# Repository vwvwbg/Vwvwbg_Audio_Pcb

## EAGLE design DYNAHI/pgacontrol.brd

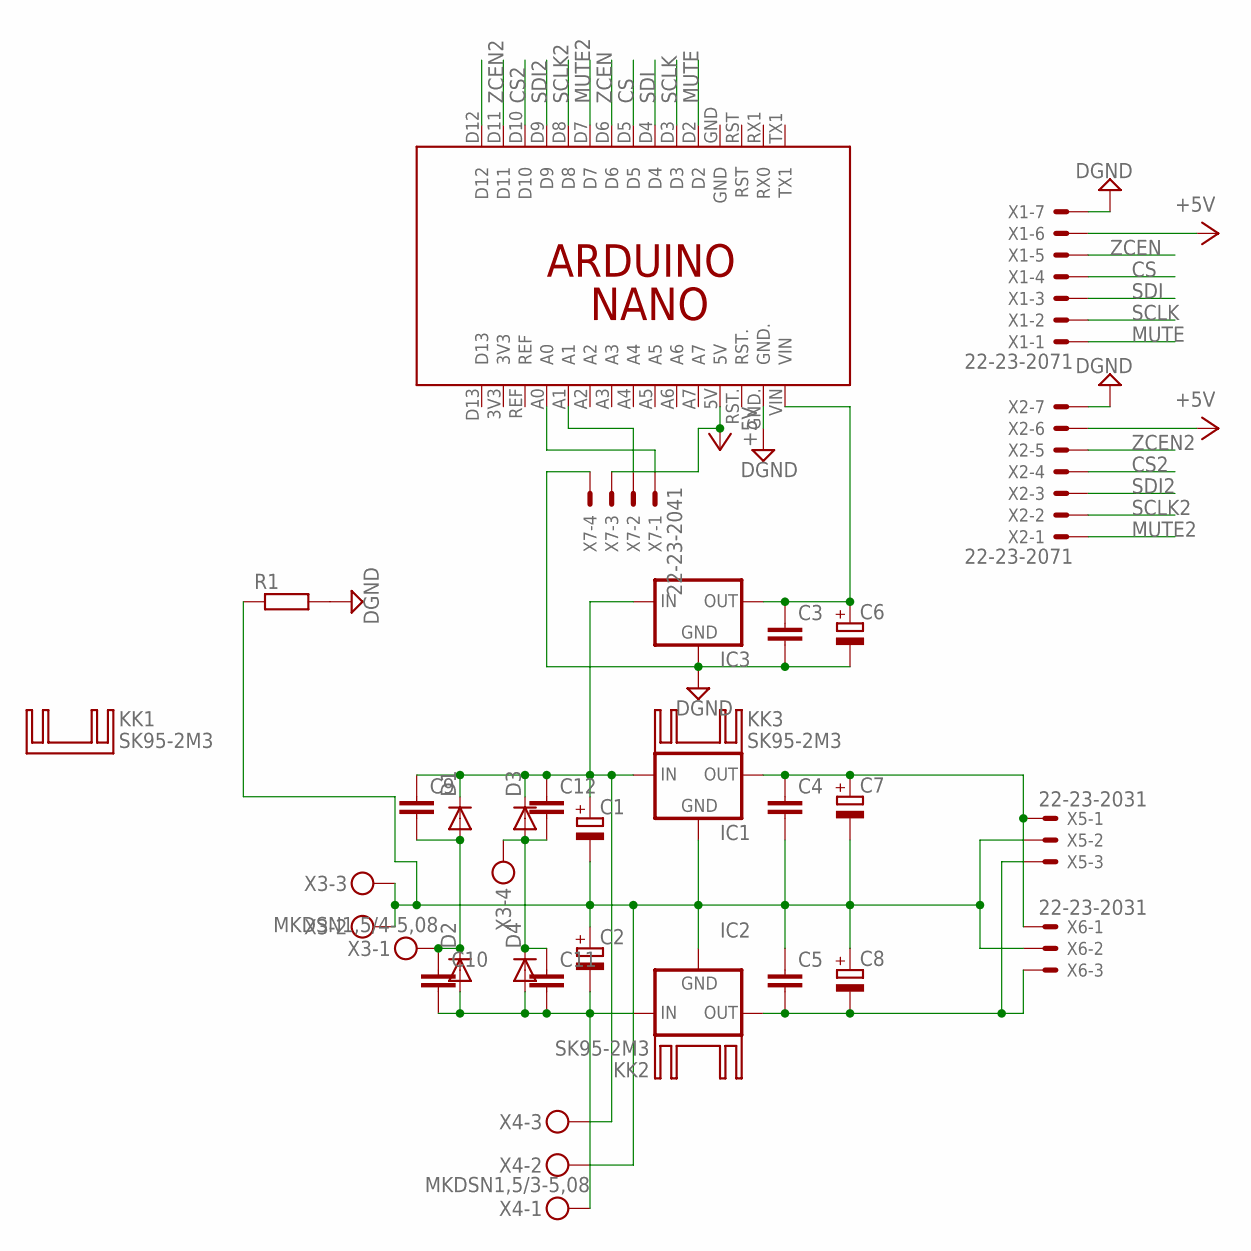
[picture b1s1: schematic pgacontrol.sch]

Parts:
C1, C2: CPOL-EUE7.5-18; E7,5-18
C3, C4, C5, C9, C10, C11, C12: C-EU050-030X075; C050-030X075
C6, C7, C8: CPOL-EUE3.5-8; E3,5-8
D1, D2, D3, D4: 1N4148DO35-10; DO35-10
IC1, IC3: 78XXS
IC2: 79XXS
KK1, KK2, KK3: SK95-2M3
PCB1: ARDUINO_NANO
R1: R-EU_0207/7; 0207/7
X1, X2: 22-23-2071
X3: MKDSN1,5/4-5,08
X4: MKDSN1,5/3-5,08
X5, X6: 22-23-2031
X7: 22-23-2041

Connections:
+5V: PCB1.5V, X1.6, X2.6, X7.3
+15: C4.1, C7.+, IC1.OUT, X5.1, X6.1
CS: PCB1.D5, X1.4
CS2: PCB1.D10, X2.4
DGND: C3.2, C6.-, IC3.GND, PCB1.GND., R1.2, X1.7, X2.7, X7.4
GND: C1.-, C2.+, C4.2, C5.1, C7.-, C8.+, IC1.GND, IC2.GND, R1.1, X3.2, X3.3, X4.2, X5.2, X6.2
MUTE: PCB1.D2, X1.1
MUTE2: PCB1.D7, X2.1
unnamed: C9.2, C10.1, D1.A, D2.C, X3.1
unnamed: PCB1.A0, X7.1
unnamed: C11.1, C12.2, D3.A, D4.C, X3.4
unnamed: PCB1.A1, X7.2
unnamed: C5.2, C8.-, IC2.OUT, X5.3, X6.3
unnamed: C3.1, C6.+, IC3.OUT, PCB1.VIN
SCLK: PCB1.D3, X1.2
SCLK2: PCB1.D8, X2.2
SDI: PCB1.D4, X1.3
SDI2: PCB1.D9, X2.3
V+: C1.+, C9.1, C12.1, D1.C, D3.C, IC1.IN, IC3.IN, X4.3
V-: C2.-, C10.2, C11.2, D2.A, D4.A, IC2.IN, X4.1
ZCEN: PCB1.D6, X1.5
ZCEN2: PCB1.D11, X2.5

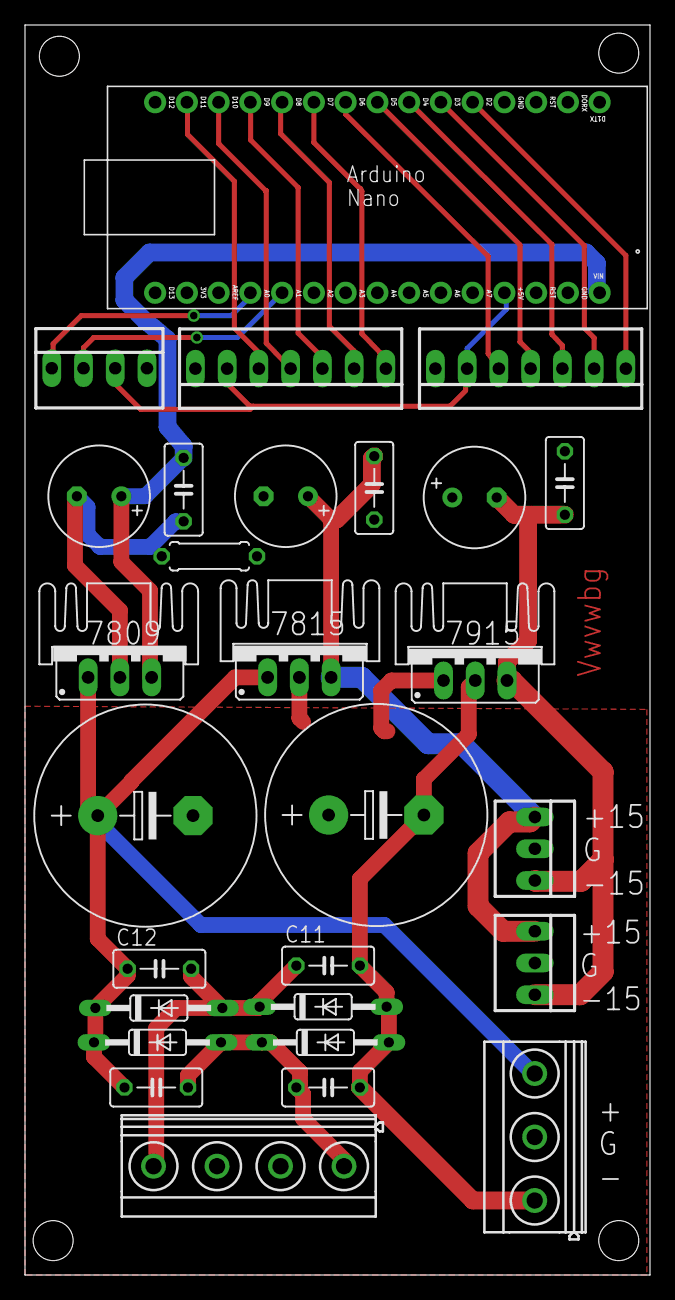
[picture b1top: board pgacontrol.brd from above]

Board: 2 copper layers, 50.0 x 100.0 mm, 31 parts (0 on the bottom side), 22 nets.

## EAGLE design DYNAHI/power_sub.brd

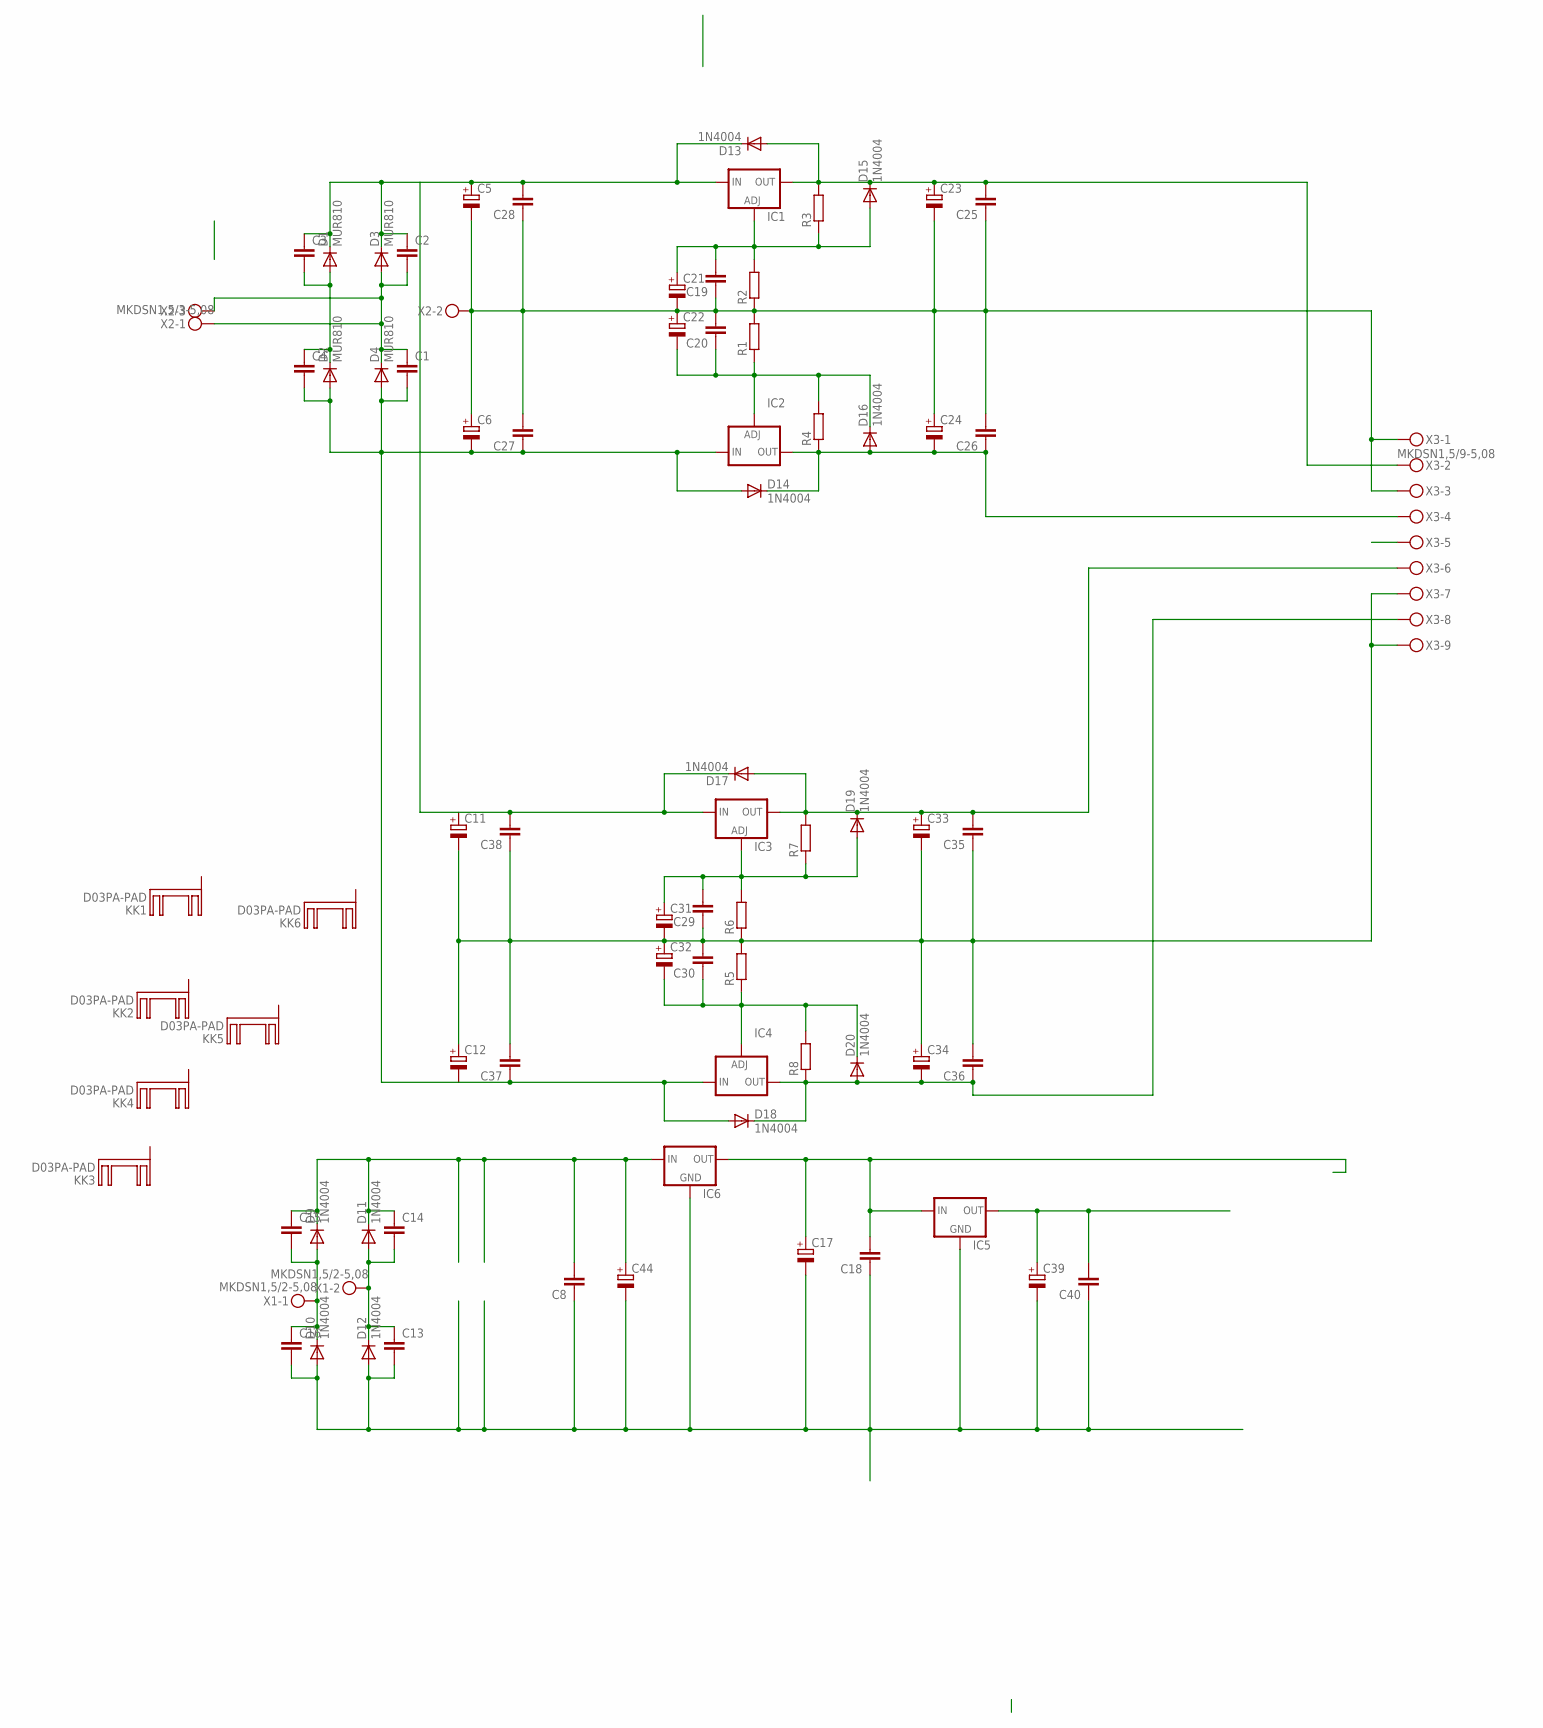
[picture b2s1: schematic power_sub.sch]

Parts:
C1, C2, C3, C4, C13, C14, C15, C16: C-EU025-025X050; C025-025X050
C5, C6, C11, C12, C44: CPOL-EUE7.5-18; E7,5-18
C8, C18, C19, C20, C25, C26, C27, C28, C29, C30, C35, C36, C37, C38, C40: C-EU050-045X075; C050-045X075
C17, C23, C24, C33, C34, C39: CPOL-EUE5-10.5; E5-10,5
C21, C22, C31, C32: CPOL-EUE5-8.5; E5-8,5
D1, D2, D3, D4: MUR810; TO220ACS
D9, D10, D11, D12, D13, D14, D15, D16, D17, D18, D19, D20: 1N4004; DO41-10
IC1, IC3: LM317TS; 317TS
IC2, IC4: LM337TS; 337TS
IC5, IC6: 78XXS
KK1, KK2, KK3, KK4, KK5, KK6: D03PA-PAD
R1, R2, R3, R4, R5, R6, R7, R8: R-EU_0207/12; 0207/12
X1: MKDSN1,5/2-5,08
X2: MKDSN1,5/3-5,08
X3: MKDSN1,5/9-5,08

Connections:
unnamed: C2.1, C3.1, C5.+, C28.2, C38.2, D1.C, D3.C, D13.C, D17.C, IC1.3 (IN), IC3.3 (IN)
unnamed: C3.2, C4.1, D1.A, D2.C
unnamed: C39.+, C40.2, IC5.OUT
unnamed: C1.1, C2.2, D3.A, D4.C, X2.1, X2.3
unnamed: C11.-, C12.+, C29.1, C30.2, C31.-, C32.+, C33.-, C34.+, C35.1, C36.2, C37.2, C38.1, R5.2, R6.1, X3.7, X3.9
unnamed: C8.2, C14.1, C15.1, C44.+, D9.C, D11.C, IC6.IN
unnamed: C15.2, C16.1, D9.A, D10.C, X1.1
unnamed: C8.1, C13.2, C16.2, C17.-, C18.1, C39.-, C40.1, C44.-, D10.A, D12.A, IC5.GND, IC6.GND
unnamed: C13.1, C14.2, D11.A, D12.C, X1.2
unnamed: C1.2, C4.2, C6.-, C27.1, C37.1, D2.A, D4.A, D14.A, D18.A, IC2.2 (IN), IC4.2 (IN)
unnamed: C23.+, C25.2, D13.A, D15.C, IC1.2 (OUT), R3.2, X3.2
unnamed: C33.+, C35.2, D17.A, D19.C, IC3.2 (OUT), R7.2, X3.6
unnamed: C20.1, C22.-, D16.C, IC2.1 (ADJ), R1.1, R4.2
unnamed: C19.2, C21.+, D15.A, IC1.1 (ADJ), R2.2, R3.1
unnamed: C5.-, C6.+, C19.1, C20.2, C21.-, C22.+, C23.-, C24.+, C25.1, C26.2, C27.2, C28.1, R1.2, R2.1, X2.2, X3.1, X3.3
unnamed: C30.1, C32.-, D20.C, IC4.1 (ADJ), R5.1, R8.2
unnamed: C29.2, C31.+, D19.A, IC3.1 (ADJ), R6.2, R7.1
unnamed: C17.+, C18.2, IC5.IN, IC6.OUT
unnamed: C24.-, C26.1, D14.C, D16.A, IC2.3 (OUT), R4.1, X3.4
unnamed: C34.-, C36.1, D18.C, D20.A, IC4.3 (OUT), R8.1, X3.8

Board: 2 copper layers, 77 parts (0 on the bottom side), 20 nets, no tracks yet.

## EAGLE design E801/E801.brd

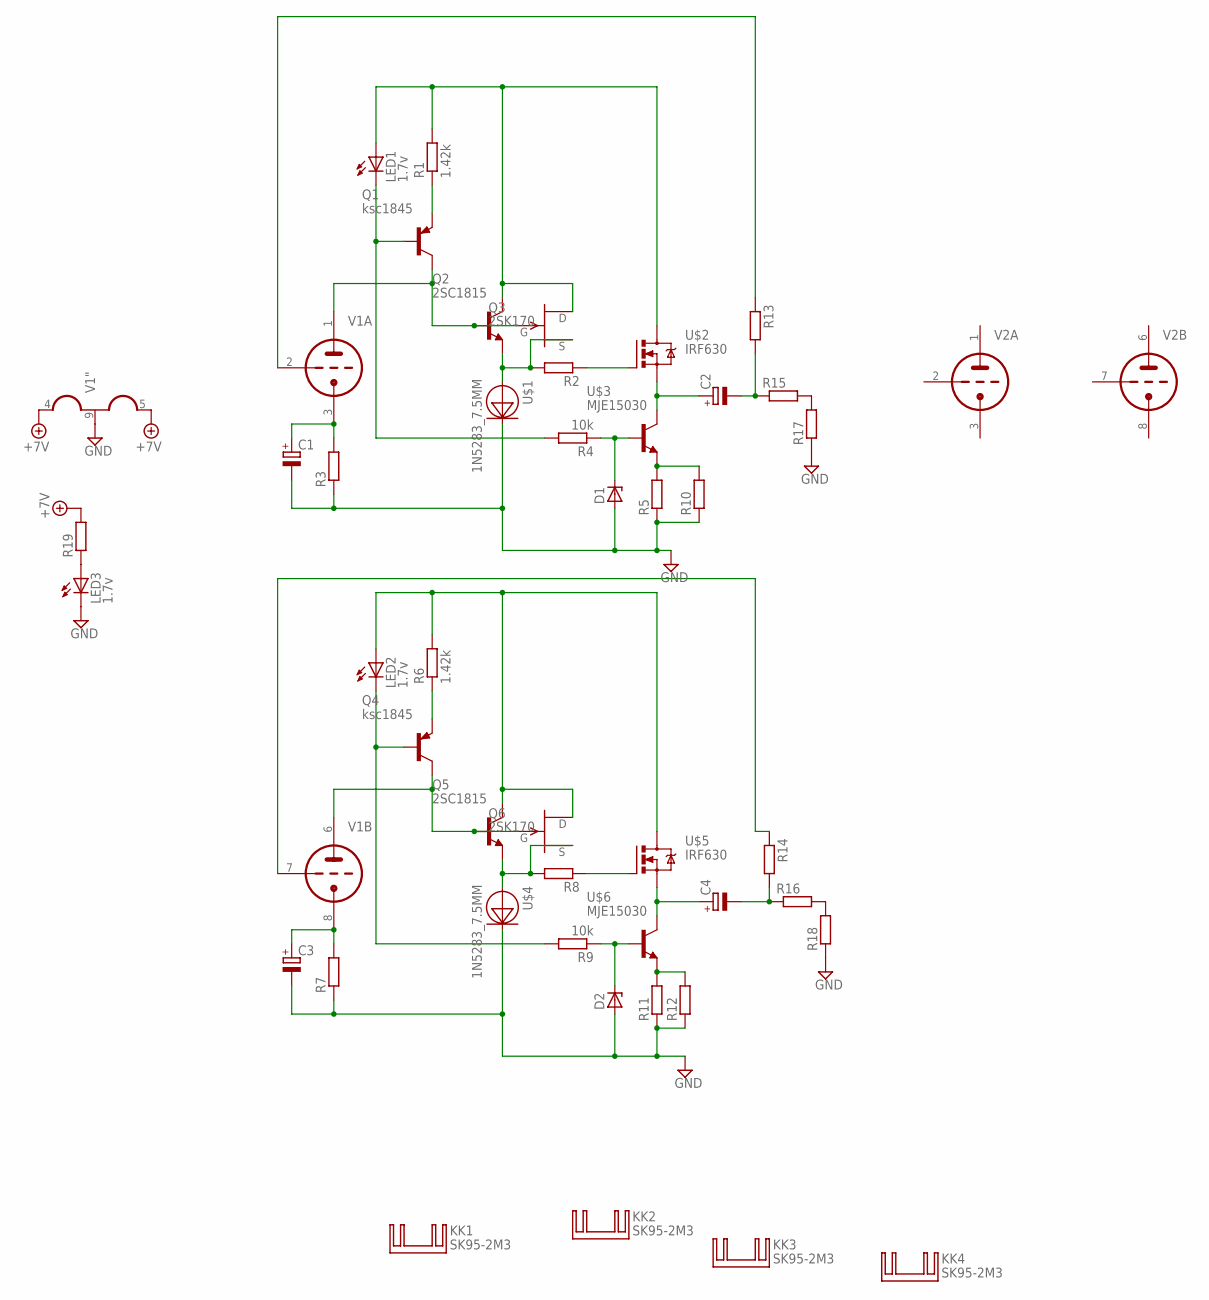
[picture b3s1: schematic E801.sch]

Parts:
C1, C3: CPOL-EUE5-10.5; E5-10,5
C2, C4: CPOL-EUE30-12AXIAL; E30-12
D1, D2: ZENER-DIODEDO34-7; DO34Z7
KK1, KK2, KK3, KK4: SK95-2M3
LED1, LED2, LED3: 1.7v; LED5MM
Q1, Q4: ksc1845; TO92-BCE
Q2, Q5: 2SC1815; TO92-ECB
Q3, Q6: 2SK170; TO92-
R1, R6: 1.42k; 0207/10
R2, R3, R5, R7, R8, R10, R11, R12, R13, R14, R15, R16, R17, R18, R19: R-EU_0207/10; 0207/10
R4, R9: 10k; 0207/10
U$1, U$4: 1N5283_7.5MM; DO-35-3
U$2, U$5: IRF630; TO220V
U$3, U$6: MJE15030; TO220KG
V1, V2: 12AU7-P; NOVAL

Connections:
+7V: R19.2, V1.4 (H1), V1.5 (H3)
GND: C1.-, C3.-, D1.A, D2.A, LED3.K (C), R3.1, R5.1, R7.1, R10.1, R11.1, R12.1, R17.1, R18.1, U$1.CATHODE, U$4.CATHODE, V1.9 (H2)
unnamed: Q1.C, Q2.B, Q3.2 (G), V1.1 (TA)
unnamed: Q1.E, R1.1
unnamed: LED1.K (C), Q1.B, R4.2
unnamed: LED1.A, Q2.C, Q3.1 (D), R1.2, U$2.2 (D)
unnamed: Q2.E, Q3.3 (S), R2.2, U$1.ANODE
unnamed: C1.+, R3.2, V1.3 (TK)
unnamed: R5.2, R10.2, U$3.3 (E)
unnamed: R11.2, R12.2, U$6.3 (E)
unnamed: C2.-, R13.2, R15.1
unnamed: Q4.C, Q5.B, Q6.2 (G), V1.6 (TA)
unnamed: R2.1, U$2.1 (G)
unnamed: Q4.E, R6.1
unnamed: C2.+, U$2.3 (S), U$3.2 (C)
unnamed: D1.C, R4.1, U$3.1 (B)
unnamed: LED2.K (C), Q4.B, R9.2
unnamed: LED2.A, Q5.C, Q6.1 (D), R6.2, U$5.2 (D)
unnamed: Q5.E, Q6.3 (S), R8.2, U$4.ANODE
unnamed: C3.+, R7.2, V1.8 (TK)
unnamed: R13.1, V1.2 (TG)
unnamed: R8.1, U$5.1 (G)
unnamed: C4.+, U$5.3 (S), U$6.2 (C)
unnamed: D2.C, R9.1, U$6.1 (B)
unnamed: C4.-, R14.2, R16.1
unnamed: R14.1, V1.7 (TG)
unnamed: R15.2, R17.2
unnamed: R16.2, R18.2
unnamed: LED3.A, R19.1

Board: 2 copper layers, 46 parts (2 on the bottom side), 29 nets, no tracks yet.

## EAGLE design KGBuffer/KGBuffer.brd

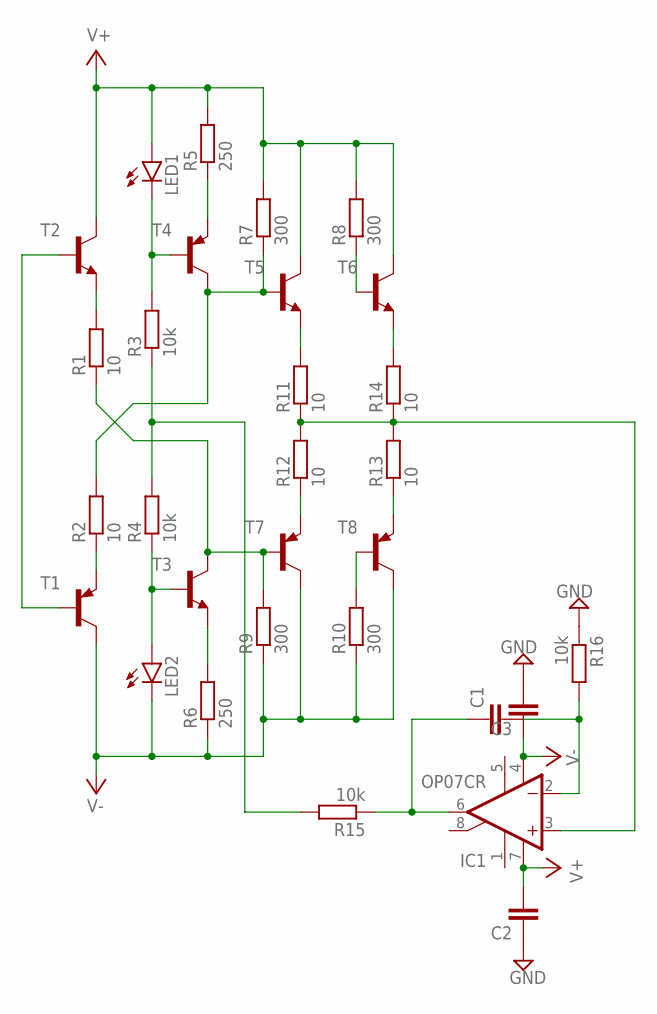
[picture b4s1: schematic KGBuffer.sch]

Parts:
C1: C-EUC0603K; C0603K
C2, C3: C-EUC0805K; C0805K
IC1: OP07CR; SO08
LED1, LED2: LEDSMT1206; 1206
R1, R2, R11, R12, R13, R14: 10; MINI_MELF-0204W
R3, R4, R15, R16: 10k; MINI_MELF-0204W
R5, R6: 250; MINI_MELF-0204W
R7, R8, R9, R10: 300; MINI_MELF-0204W
T1, T4, T7, T8: BC856BLT1-PNP-SOT23-BEC; SOT23-BEC
T2, T3, T5, T6: BC846-NPN-SOT23-BEC; SOT23-BEC

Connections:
GND: C2.1, C3.2, R16.1
unnamed: T1.B, T2.B
unnamed: R2.1, T1.E
unnamed: R1.2, T2.E
unnamed: C1.1, IC1.6 (OUT), R15.1
unnamed: LED1.C, R3.2, T4.B
unnamed: R5.1, T4.E
unnamed: R2.2, R7.1, T4.C, T5.B
unnamed: R6.2, T3.E
unnamed: LED2.A, R4.1, T3.B
unnamed: R1.1, R9.2, T3.C, T7.B
unnamed: R3.1, R4.2, R15.2
unnamed: R10.2, T8.B
unnamed: C1.2, IC1.2 (-IN), R16.2
unnamed: R8.1, T6.B
unnamed: R11.2, T5.E
unnamed: R12.1, T7.E
unnamed: R13.1, T8.E
unnamed: R14.2, T6.E
unnamed: IC1.3 (+IN), R11.1, R12.2, R13.2, R14.1
V+: C2.2, IC1.7 (V+), LED1.A, R5.2, R7.2, R8.2, T2.C, T5.C, T6.C
V-: C3.1, IC1.4 (V-), LED2.C, R6.1, R9.1, R10.1, T1.C, T7.C, T8.C

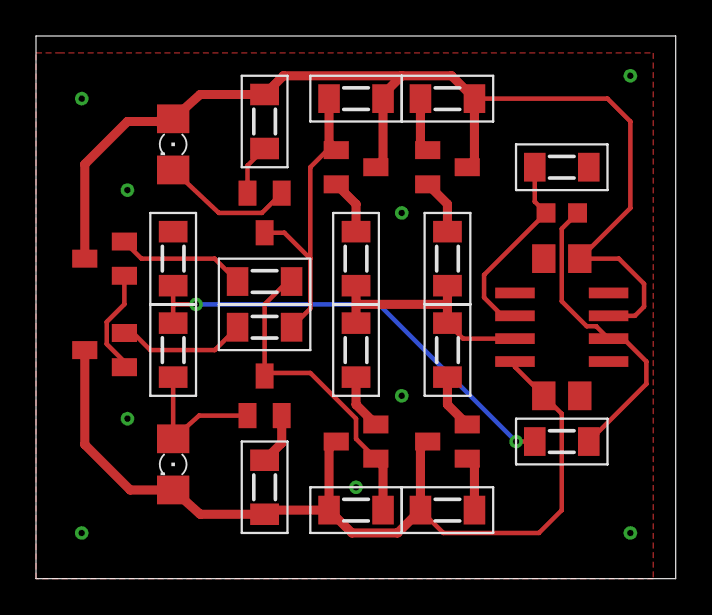
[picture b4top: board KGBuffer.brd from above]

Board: 2 copper layers, 35.5 x 30.1 mm, 30 parts (0 on the bottom side), 22 nets.

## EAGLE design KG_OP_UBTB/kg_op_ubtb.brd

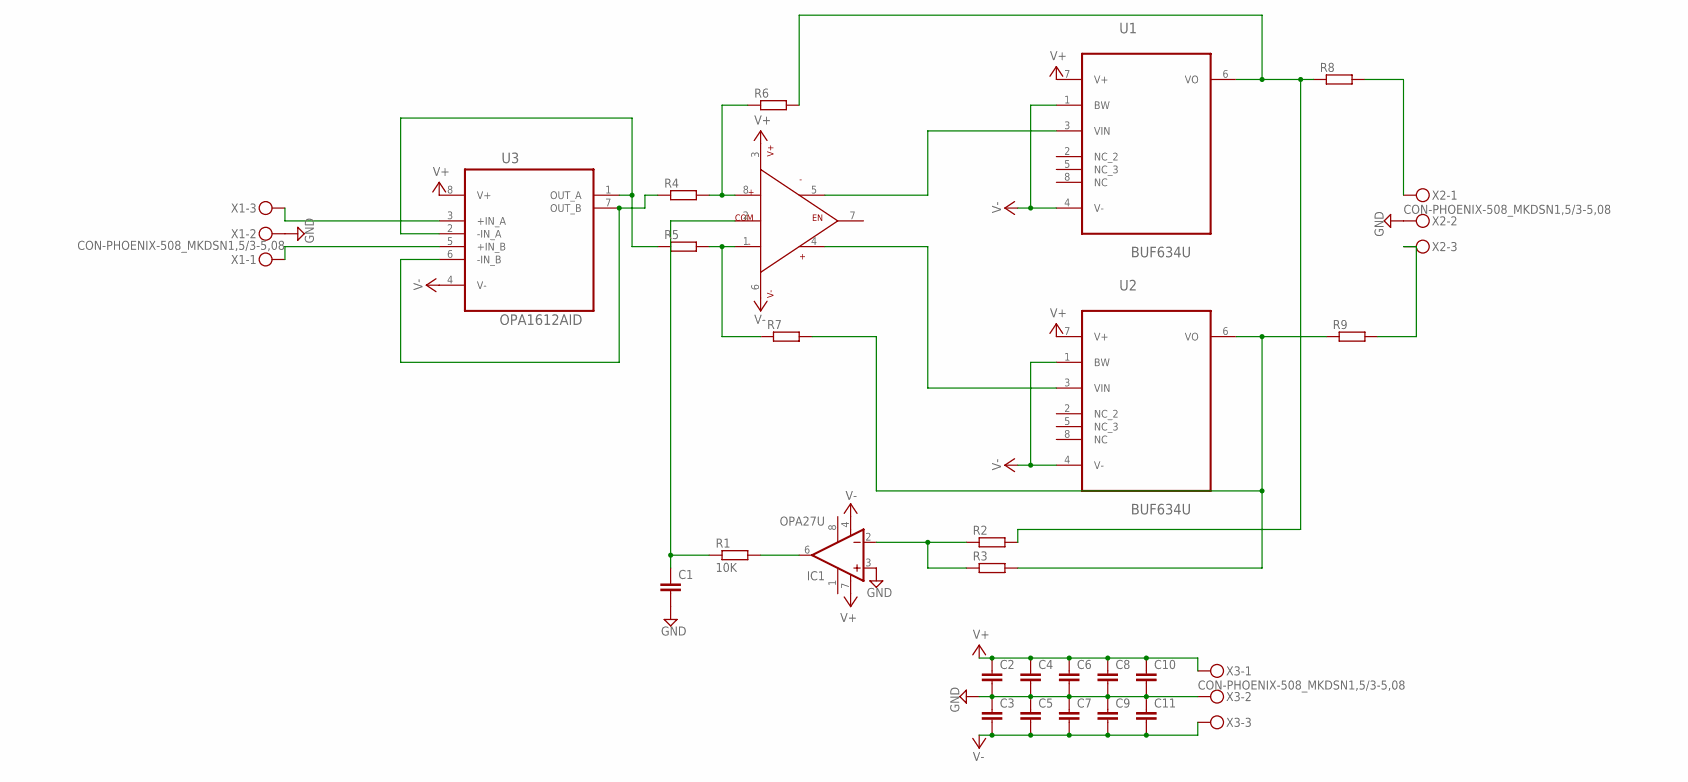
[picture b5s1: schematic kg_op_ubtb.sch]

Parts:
C1, C2, C3, C4, C5, C6, C7, C8, C9, C10, C11: C-EUC0805; C0805
IC1: OPA27U; SO08
R1: 10K; MINI_MELF-0204W
R2, R3, R4, R5, R6, R7, R8, R9: R-EU_MELF0204W; MINI_MELF-0204W
U1, U2: BUF634U; SOIC127P600X175-8N
U3: OPA1612AID; SOIC127P600X175-8N
U$1: OPA1632; SO8
X1, X2, X3: CON-PHOENIX-508_MKDSN1,5/3-5,08

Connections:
GND: C1.2, C2.2, C3.1, C4.2, C5.1, C6.2, C7.1, C8.2, C9.1, C10.2, C11.1, IC1.3 (+IN), X1.2, X2.2, X3.2
unnamed: U1.3 (VIN), U$1.5 (OUT-)
unnamed: U2.3 (VIN), U$1.4 (OUT+)
unnamed: R5.1, U3.1 (OUT_A), U3.2 (-IN_A)
unnamed: R4.1, U3.6 (-IN_B), U3.7 (OUT_B)
unnamed: R4.2, R6.1, U$1.8 (IN+)
unnamed: U3.3 (+IN_A), X1.3
unnamed: U3.5 (+IN_B), X1.1
unnamed: R5.2, R7.1, U$1.1 (IN-)
unnamed: C1.1, R1.1, U$1.2 (COM)
unnamed: IC1.6 (OUT), R1.2
unnamed: IC1.2 (-IN), R2.1, R3.1
unnamed: R3.2, R7.2, R9.1, U2.6 (VO)
unnamed: R2.2, R6.2, R8.1, U1.6 (VO)
unnamed: R9.2, X2.3
unnamed: R8.2, X2.1
V+: C2.1, C4.1, C6.1, C8.1, C10.1, IC1.7 (V+), U1.7 (V+), U2.7 (V+), U3.8 (V+), U$1.3 (V+), X3.1
V-: C3.2, C5.2, C7.2, C9.2, C11.2, IC1.4 (V-), U1.1 (BW), U1.4 (V-), U2.1 (BW), U2.4 (V-), U3.4 (V-), U$1.6 (V-), X3.3

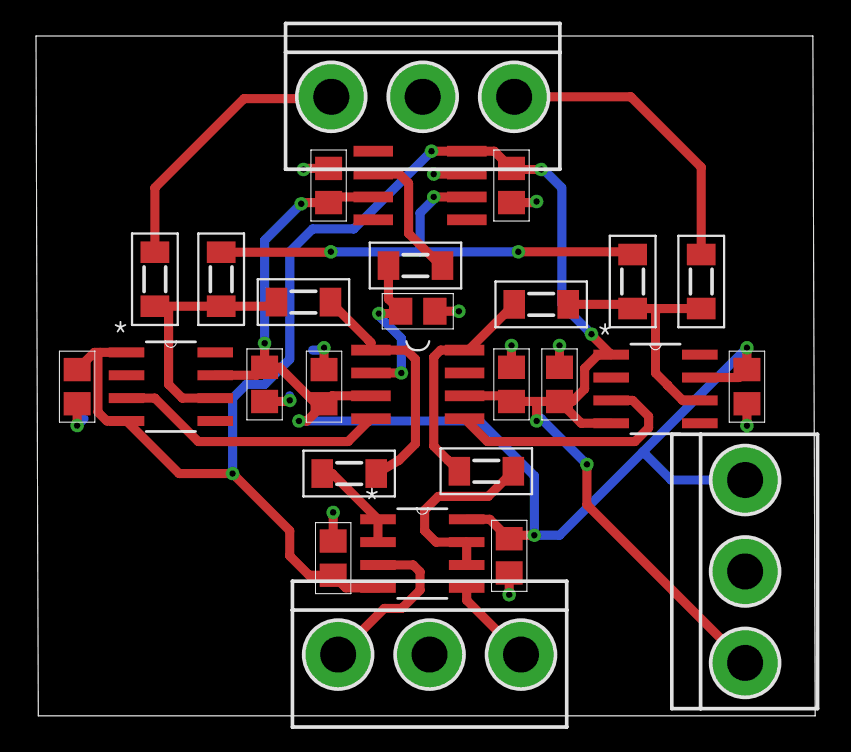
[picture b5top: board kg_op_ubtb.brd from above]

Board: 2 copper layers, 43.3 x 37.8 mm, 28 parts (0 on the bottom side), 18 nets.

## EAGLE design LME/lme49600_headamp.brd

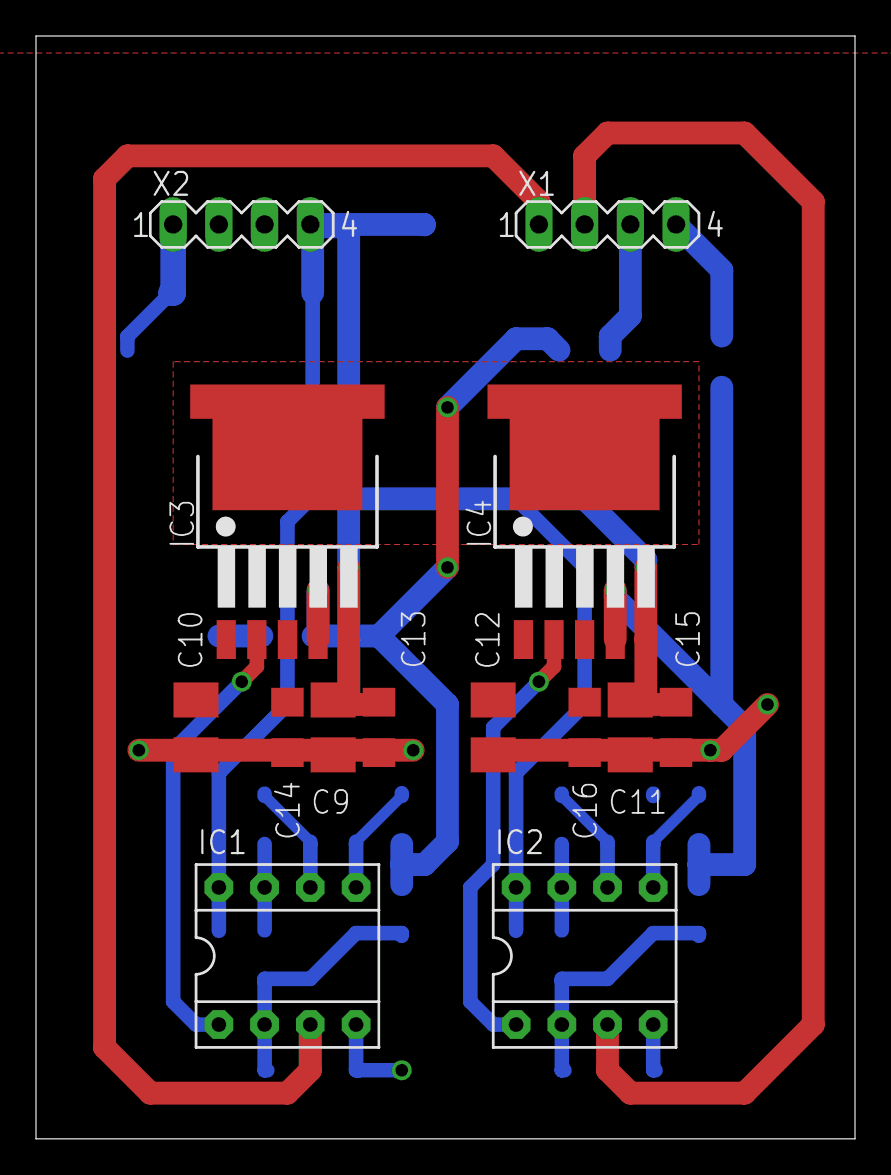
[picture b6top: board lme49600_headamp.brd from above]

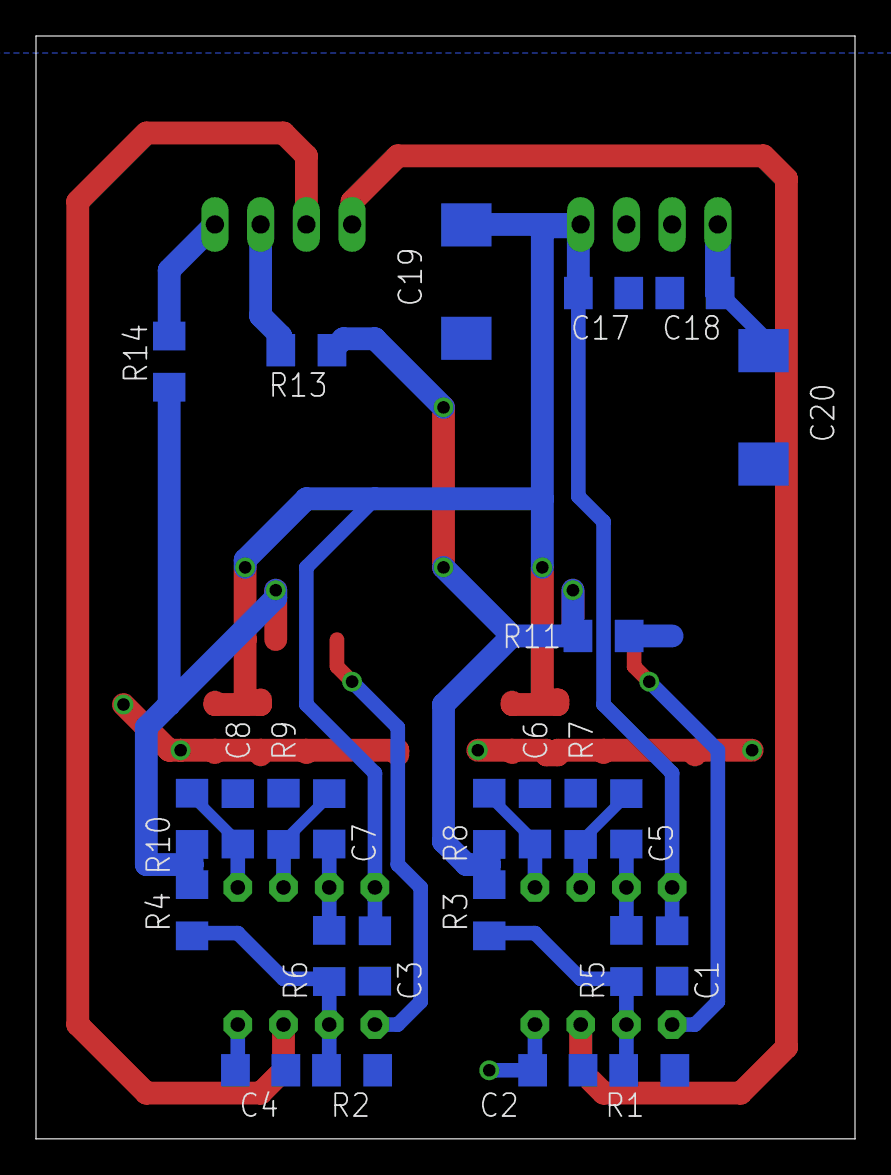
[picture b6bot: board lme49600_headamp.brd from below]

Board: 2 copper layers, 45.5 x 61.3 mm, 39 parts (25 on the bottom side), 19 nets.

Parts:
C1, C2, C3, C4, C5, C6, C7, C8: 1uF; C1206
C9, C10, C11, C12: 4u7/25V; B/3528-21R
C13, C14, C15, C16, C17, C18: 100nF; C1206
C19, C20: 100uF/16V; SMC_D
IC1, IC2: LME49720; DIL08
IC3, IC4: LME49600; TS5B
R1, R2, R3, R4, R5, R6: 1k; R1206
R7, R8, R9, R10: 1M; R1206
R11, R13, R14: 10R; R1206
X1, X2: S1G4; MA04-1

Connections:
GND: C1.2, C2.2, C3.2, C4.2, C6.2, C8.2, C9.-, C10.+, C11.-, C12.+, C13.2, C14.2, C15.2, C16.2, C17.2, C18.1, C19.-, C20.+, R1.1, R2.1, R7.1, R9.1, X2.2, X2.3
LOUT: R13.2, X1.3
unnamed: IC1.1, IC3.2
unnamed: IC2.3, X1.2
unnamed: IC1.2, R1.2, R3.1, R5.2
unnamed: IC2.1, IC4.2
unnamed: IC3.4, R3.2, R8.1, R11.2, R13.1
unnamed: IC1.3, X1.1
unnamed: C5.1, IC1.6, R7.2
unnamed: C6.1, IC1.5, R8.2
unnamed: C5.2, IC1.7, R5.1
unnamed: IC2.2, R2.2, R4.1, R6.2
unnamed: C7.2, IC2.7, R6.1
unnamed: C7.1, IC2.6, R9.2
unnamed: C8.1, IC2.5, R10.2
unnamed: IC4.4, R4.2, R10.1, R14.1
ROUT: R14.2, X1.4
VCC: C1.1, C3.1, C9.+, C11.+, C13.1, C15.1, C17.1, C19.+, IC1.8, IC2.8, IC3.5, IC4.5, X2.4
VEE: C2.1, C4.1, C10.-, C12.-, C14.1, C16.1, C18.2, C20.-, IC1.4, IC2.4, IC3.1, IC3.3, IC3.TH@1, IC3.TH@2, IC4.1, IC4.3, IC4.TH@1, IC4.TH@2, X2.1

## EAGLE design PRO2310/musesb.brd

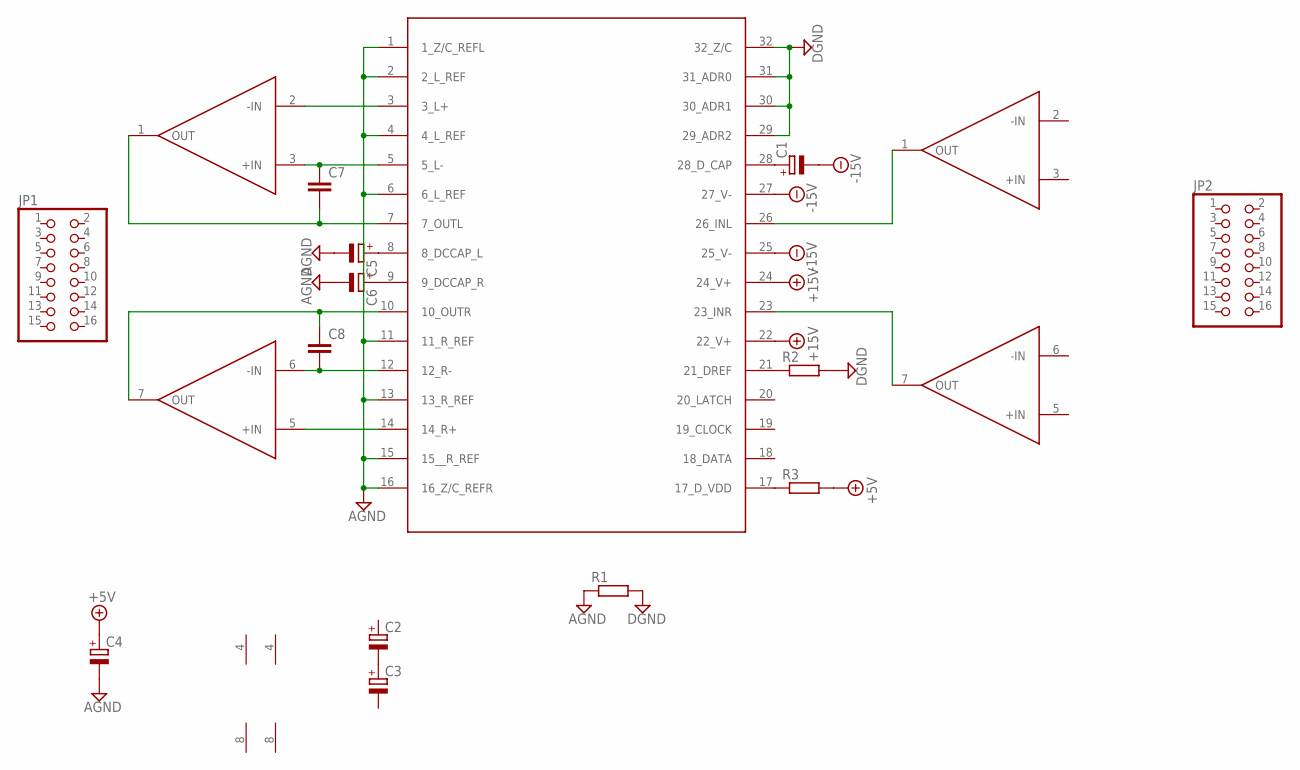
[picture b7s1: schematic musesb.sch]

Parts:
C1: CPOL-EUE2.5-6; E2,5-6
C2, C3, C4, C5, C6: CPOL-EUE3.5-8; E3,5-8
C7, C8: C-EU025-025X050; C025-025X050
JP1, JP2: PINHD-2X8; 2X08
R1, R2, R3: R-EU_0207/7; 0207/7
U$1: MUSES72320; SSOP28DB
U$2, U$3: LME49720; DIL08

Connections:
+5V: C4.+, R3.2
+15V: U$1.22 (22_V+), U$1.24 (24_V+)
-15V: C1.-, U$1.25 (25_V-), U$1.27 (27_V-)
AGND: C4.-, C5.-, C6.-, R1.1, U$1.1 (1_Z/C_REFL), U$1.2 (2_L_REF), U$1.4 (4_L_REF), U$1.6 (6_L_REF), U$1.11 (11_R_REF), U$1.13 (13_R_REF), U$1.15 (15__R_REF), U$1.16 (16_Z/C_REFR)
DGND: R1.2, R2.2, U$1.29 (29_ADR2), U$1.30 (30_ADR1), U$1.31 (31_ADR0), U$1.32 (32_Z/C)
unnamed: U$1.3 (3_L+), U$2.2 (-IN)
unnamed: C7.1, U$1.5 (5_L-), U$2.3 (+IN)
unnamed: U$1.14 (14_R+), U$2.5 (+IN)
unnamed: C8.2, U$1.12 (12_R-), U$2.6 (-IN)
unnamed: U$1.23 (23_INR), U$3.7 (OUT)
unnamed: U$1.26 (26_INL), U$3.1 (OUT)
unnamed: R2.1, U$1.21 (21_DREF)
unnamed: R3.1, U$1.17 (17_D_VDD)
unnamed: C1.+, U$1.28 (28_D_CAP)
unnamed: C2.-, C3.+
unnamed: C5.+, U$1.8 (8_DCCAP_L)
unnamed: C6.+, U$1.9 (9_DCCAP_R)
unnamed: C8.1, U$1.10 (10_OUTR), U$2.7 (OUT)
unnamed: C7.2, U$1.7 (7_OUTL), U$2.1 (OUT)

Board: 2 copper layers, 16 parts (0 on the bottom side), 19 nets, no tracks yet.

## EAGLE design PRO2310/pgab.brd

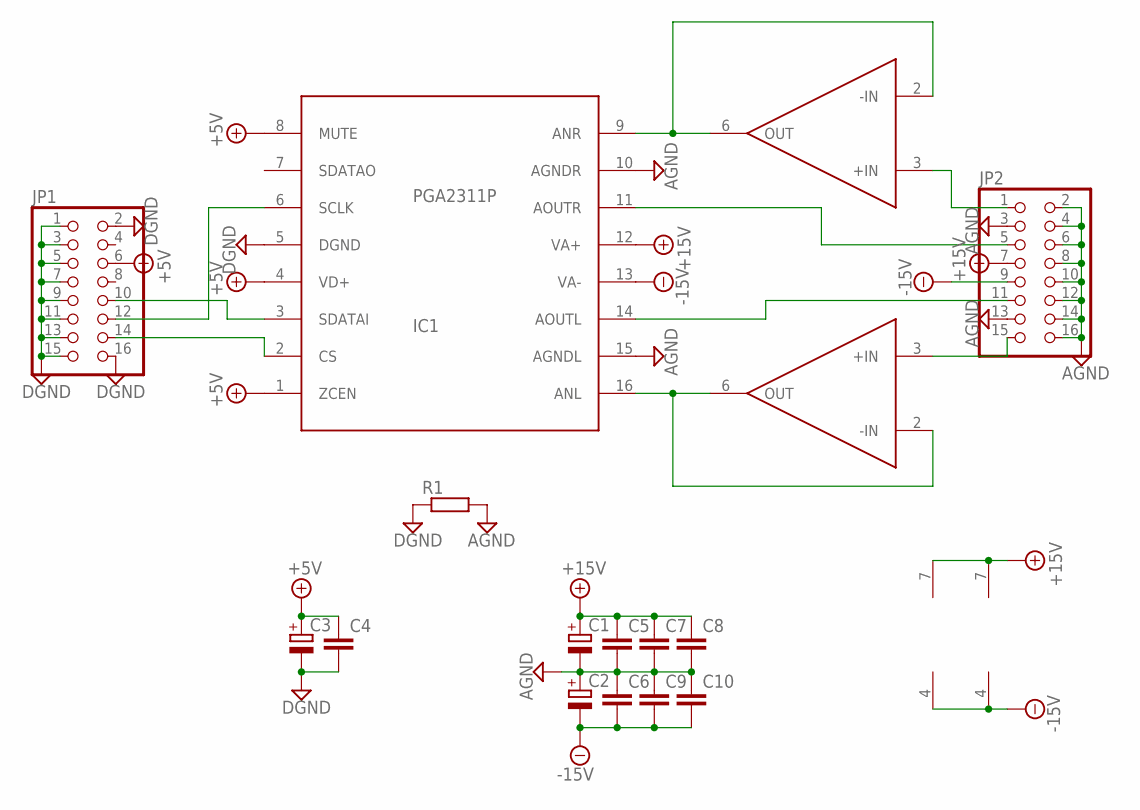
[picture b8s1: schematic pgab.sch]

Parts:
C1, C2, C3: CPOL-EUE3.5-8; E3,5-8
C4, C5, C6, C7, C8, C9, C10: C-EU025-025X050; C025-025X050
IC1: PGA2311P; DIL16
JP1, JP2: PINHD-2X8; 2X08
R1: R-EU_0207/10; 0207/10
U1, U2: OPA627BP; DIL08

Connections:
+5V: C3.+, C4.1, IC1.1 (ZCEN), IC1.4 (VD+), IC1.8 (MUTE), JP1.6
+15V: C1.+, C5.1, C7.1, C8.1, IC1.12 (VA+), JP2.7, U1.7 (V+), U2.7 (V+)
-15V: C2.-, C6.2, C9.2, C10.2, IC1.13 (VA-), JP2.9, U1.4 (V-), U2.4 (V-)
AGND: C1.-, C2.+, C5.2, C6.1, C7.2, C8.2, C9.1, C10.1, IC1.10 (AGNDR), IC1.15 (AGNDL), JP2.2, JP2.3, JP2.4, JP2.6, JP2.8, JP2.10, JP2.12, JP2.13, JP2.14, JP2.16, R1.2
DGND: C3.-, C4.2, IC1.5 (DGND), JP1.1, JP1.2, JP1.3, JP1.5, JP1.7, JP1.9, JP1.11, JP1.13, JP1.15, JP1.16, R1.1
unnamed: IC1.2 (CS), JP1.14
unnamed: IC1.3 (SDATAI), JP1.10
unnamed: IC1.6 (SCLK), JP1.12
unnamed: IC1.16 (ANL), U2.2 (-IN), U2.6 (OUT)
unnamed: IC1.9 (ANR), U1.2 (-IN), U1.6 (OUT)
unnamed: JP2.15, U2.3 (+IN)
unnamed: IC1.14 (AOUTL), JP2.11
unnamed: IC1.11 (AOUTR), JP2.5
unnamed: JP2.1, U1.3 (+IN)

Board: 2 copper layers, 16 parts (0 on the bottom side), 14 nets, no tracks yet.
